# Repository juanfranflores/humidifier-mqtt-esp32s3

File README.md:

# To do list:
- Falta agregar lectura de los leds de entrada (on y dry) y programar lógica y publicación de estados.

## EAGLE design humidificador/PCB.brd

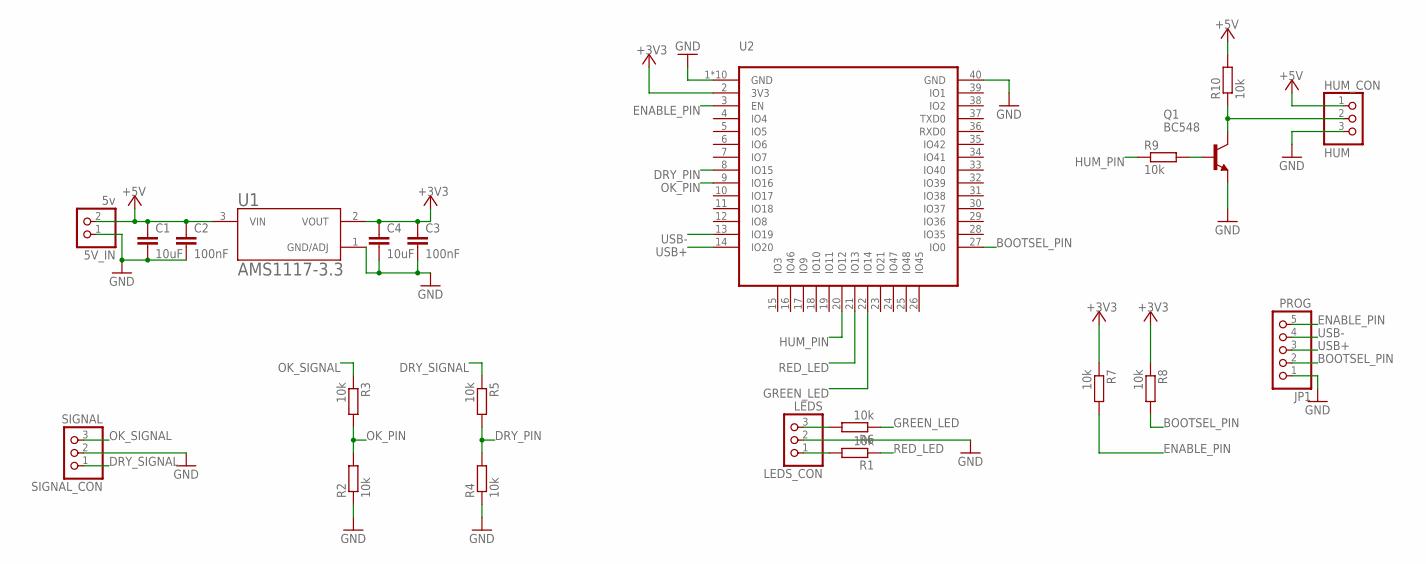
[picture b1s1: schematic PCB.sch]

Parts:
5V_IN: 5v; 1X02
C1, C4: 10uF; C1206
C2, C3: 100nF; C1206
HUM_CON: HUM; 1X03
JP1: PROG; 1X05
LEDS_CON: LEDS; 1X03
Q1: BC548; TO92-EBC
R1, R2, R3, R4, R5, R6, R7, R8, R9, R10: 10k; R1206
SIGNAL_CON: SIGNAL; 1X03
U1: AMS1117-3.3; SOT229P700X180-4N
U2: ESP32-S3-WROOM-1

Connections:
+3V3: C3.1, C4.1, R7.1, R8.1, U1.2 (VOUT), U2.2 (3V3)
+5V: 5V_IN.2, C1.1, C2.1, HUM_CON.1, R10.2, U1.3 (VIN)
BOOTSEL_PIN: JP1.2, R8.2, U2.27 (IO0)
DRY_PIN: R4.2, R5.2, U2.8 (IO15)
DRY_SIGNAL: R5.1, SIGNAL_CON.1
ENABLE_PIN: JP1.5, R7.2, U2.3 (EN)
GND: 5V_IN.1, C1.2, C2.2, C3.2, C4.2, HUM_CON.3, JP1.1, LEDS_CON.2, Q1.E, R2.1, R4.1, SIGNAL_CON.2, U1.1 (GND/ADJ), U2.1 (GND), U2.40 (GND), U2.P$1 (GND), U2.P$2 (GND), U2.P$3 (GND), U2.P$4 (GND), U2.P$5 (GND), U2.P$6 (GND), U2.P$7 (GND), U2.P$8 (GND), U2.P$9 (GND)
GREEN_LED: R6.1, U2.22 (IO14)
HUM_PIN: R9.1, U2.20 (IO12)
unnamed: LEDS_CON.3, R6.2
unnamed: LEDS_CON.1, R1.2
unnamed: Q1.B, R9.2
unnamed: HUM_CON.2, Q1.C, R10.1
OK_PIN: R2.2, R3.2, U2.9 (IO16)
OK_SIGNAL: R3.1, SIGNAL_CON.3
RED_LED: R1.1, U2.21 (IO13)
USB+: JP1.3, U2.14 (IO20)
USB-: JP1.4, U2.13 (IO19)

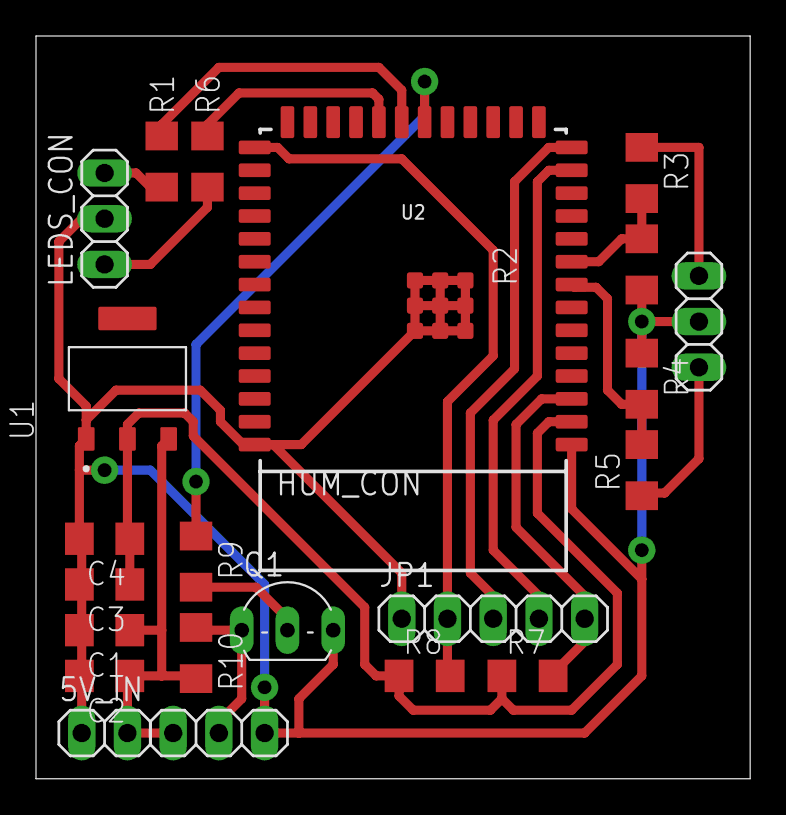
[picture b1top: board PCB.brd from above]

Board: 2 copper layers, 39.7 x 41.3 mm, 22 parts (0 on the bottom side), 18 nets.

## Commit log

2023-11-21 creo README.md
2023-11-23 modificacion
2023-11-26 agrego tópico de estado y leds
2023-11-28 con manejo de dry signal
2024-01-23 falta sacar el bug de dry después de los 15 segundos
2024-01-23 arreglo otawebserver y bug de drysignal
